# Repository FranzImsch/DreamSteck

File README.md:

### 3x3 Macro Pad

Based on nRF52840

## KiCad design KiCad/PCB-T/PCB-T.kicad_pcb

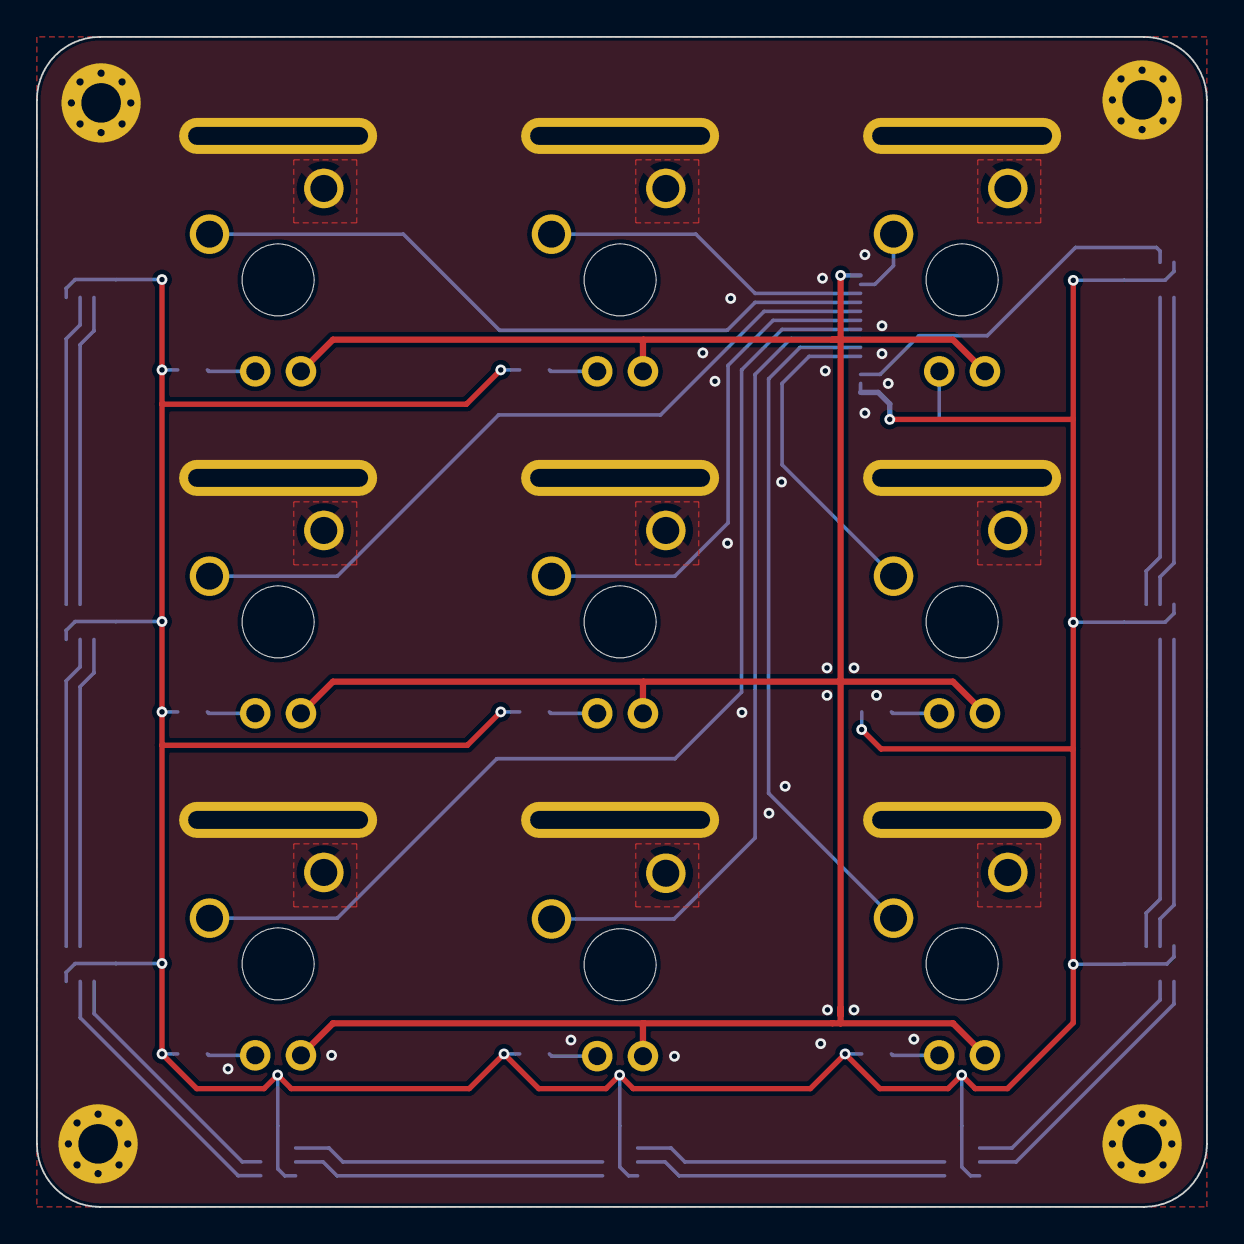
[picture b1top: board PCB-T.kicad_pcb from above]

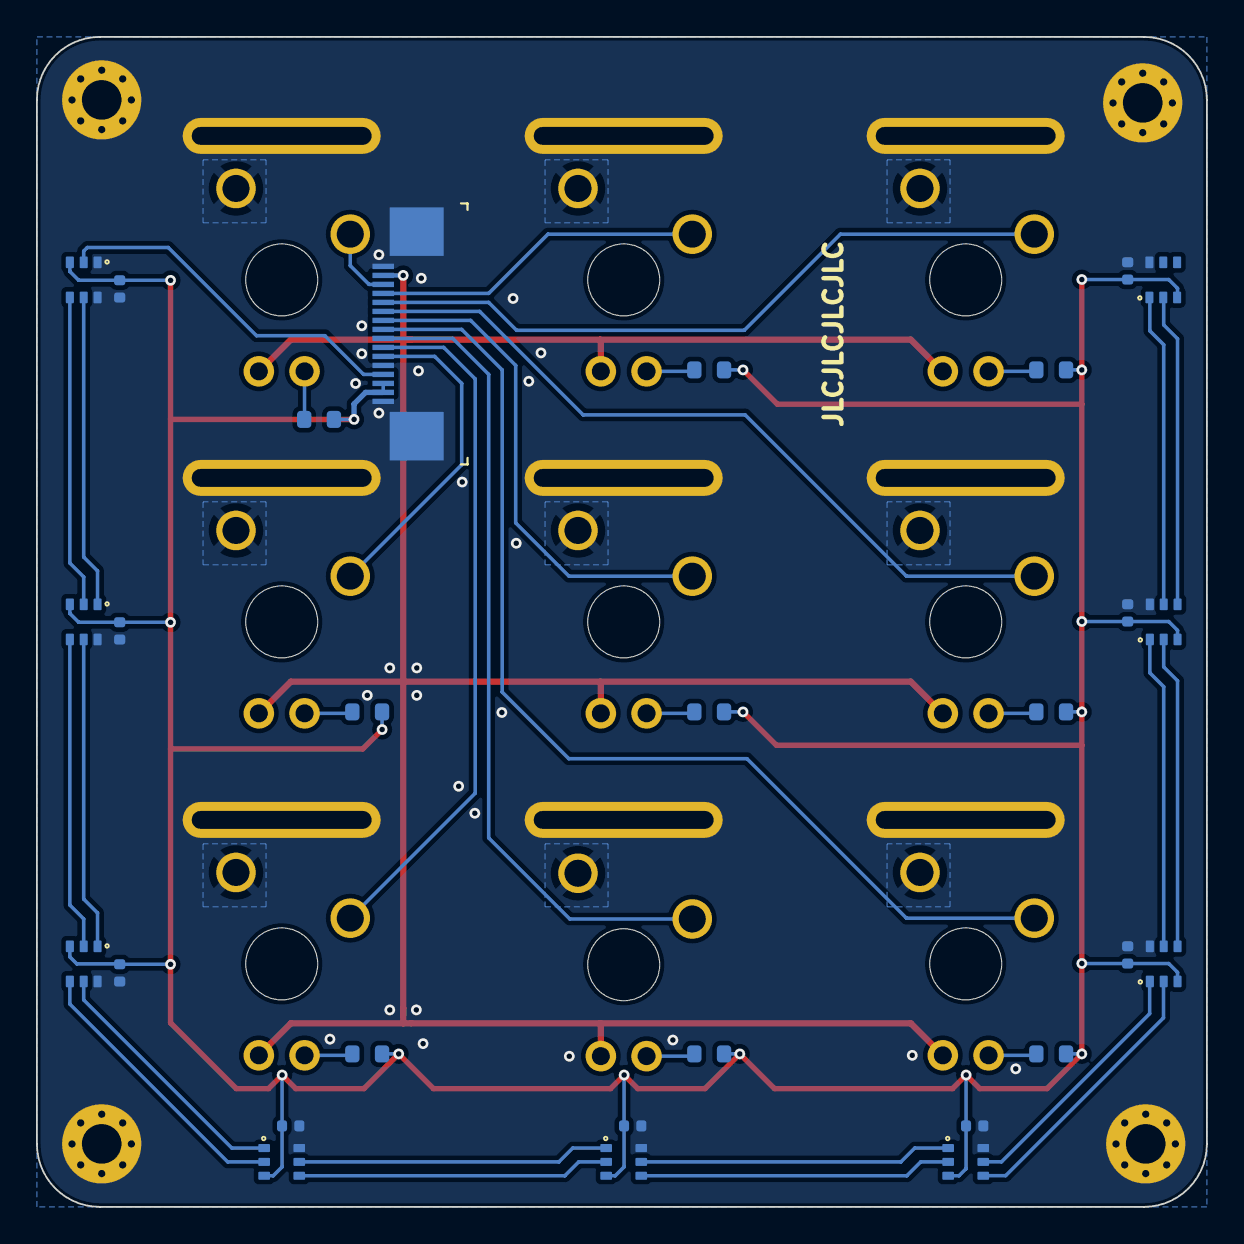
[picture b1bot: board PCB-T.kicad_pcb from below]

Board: 2 copper layers, 65.0 x 65.0 mm, 50 parts (32 on the bottom side), 21 nets.

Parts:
C37, C38, C39, C40, C41, C42, C43, C44, C45: 100n; C_0402_1005Metric_NoSilk
H5, H6, H7, H8: M2; MountingHole_2.2mm_M2_Pad_Via_NoSilk
J5: Conn_01x16_MountingPin; 68711614022
J6, J7, J8, J9, J10, J11, J12, J13, J14: OLED Slot; Plated_Slot_10x1mm
R33, R35, R36, R37, R38, R39, R40, R41, R42: R_Small; R_0603_1608Metric_NoSilk
SW2, SW3, SW4, SW5, SW6, SW7, SW8, SW9, SW10: MX Blue (LED); SW_Cherry_MX_1.00u_Plate_NoSilk
U9, U10, U11, U12, U13, U14, U15, U16, U17: WS2816

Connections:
GND: C37.2, C38.2, C39.2, C40.2, C41.2, C42.2, C43.2, C44.2, C45.2, H5.1, H6.1, H7.1, H8.1, J5.1, J5.5, J5.16, J5.MP (MountPin), J6.1, J7.1, J8.1, J9.1, J10.1, J11.1, J12.1, J13.1, J14.1, SW2.1, SW3.1, SW4.1, SW5.1, SW6.1, SW7.1, SW8.1, SW9.1, SW10.1, U9.1 (BI), U9.6 (GND), U10.6 (GND), U11.6 (GND), U12.6 (GND), U13.6 (GND), U14.6 (GND), U15.6 (GND), U16.6 (GND), U17.6 (GND)
LED-VCC: C37.1, C38.1, C39.1, C40.1, C41.1, C42.1, C43.1, C44.1, C45.1, J5.2, J5.3, R33.1, R35.1, R36.1, R37.1, R38.1, R39.1, R40.1, R41.1, R42.1, U9.3 (VCC), U10.3 (VCC), U11.3 (VCC), U12.3 (VCC), U13.3 (VCC), U14.3 (VCC), U15.3 (VCC), U16.3 (VCC), U17.3 (VCC)
LEDs_N: J5.15, SW2.3 (K), SW3.3 (K), SW4.3 (K), SW5.3 (K), SW6.3 (K), SW7.3 (K), SW8.3 (K), SW9.3 (K), SW10.3 (K)
unnamed: R33.2, SW2.4 (A)
unnamed: R35.2, SW3.4 (A)
unnamed: R36.2, SW4.4 (A)
unnamed: R37.2, SW5.4 (A)
unnamed: R38.2, SW6.4 (A)
unnamed: R39.2, SW7.4 (A)
unnamed: R40.2, SW8.4 (A)
unnamed: R41.2, SW9.4 (A)
SW1: J5.6, SW9.2
SW2: J5.7, SW10.2
SW3: J5.8, SW7.2
SW4: J5.9, SW4.2
SW5: J5.10, SW6.2
SW6: J5.11, SW3.2
SW7: J5.12, SW2.2
SW8: J5.13, SW5.2
SW9: J5.14, SW8.2
WS-DATA: J5.4, U9.2 (DI)

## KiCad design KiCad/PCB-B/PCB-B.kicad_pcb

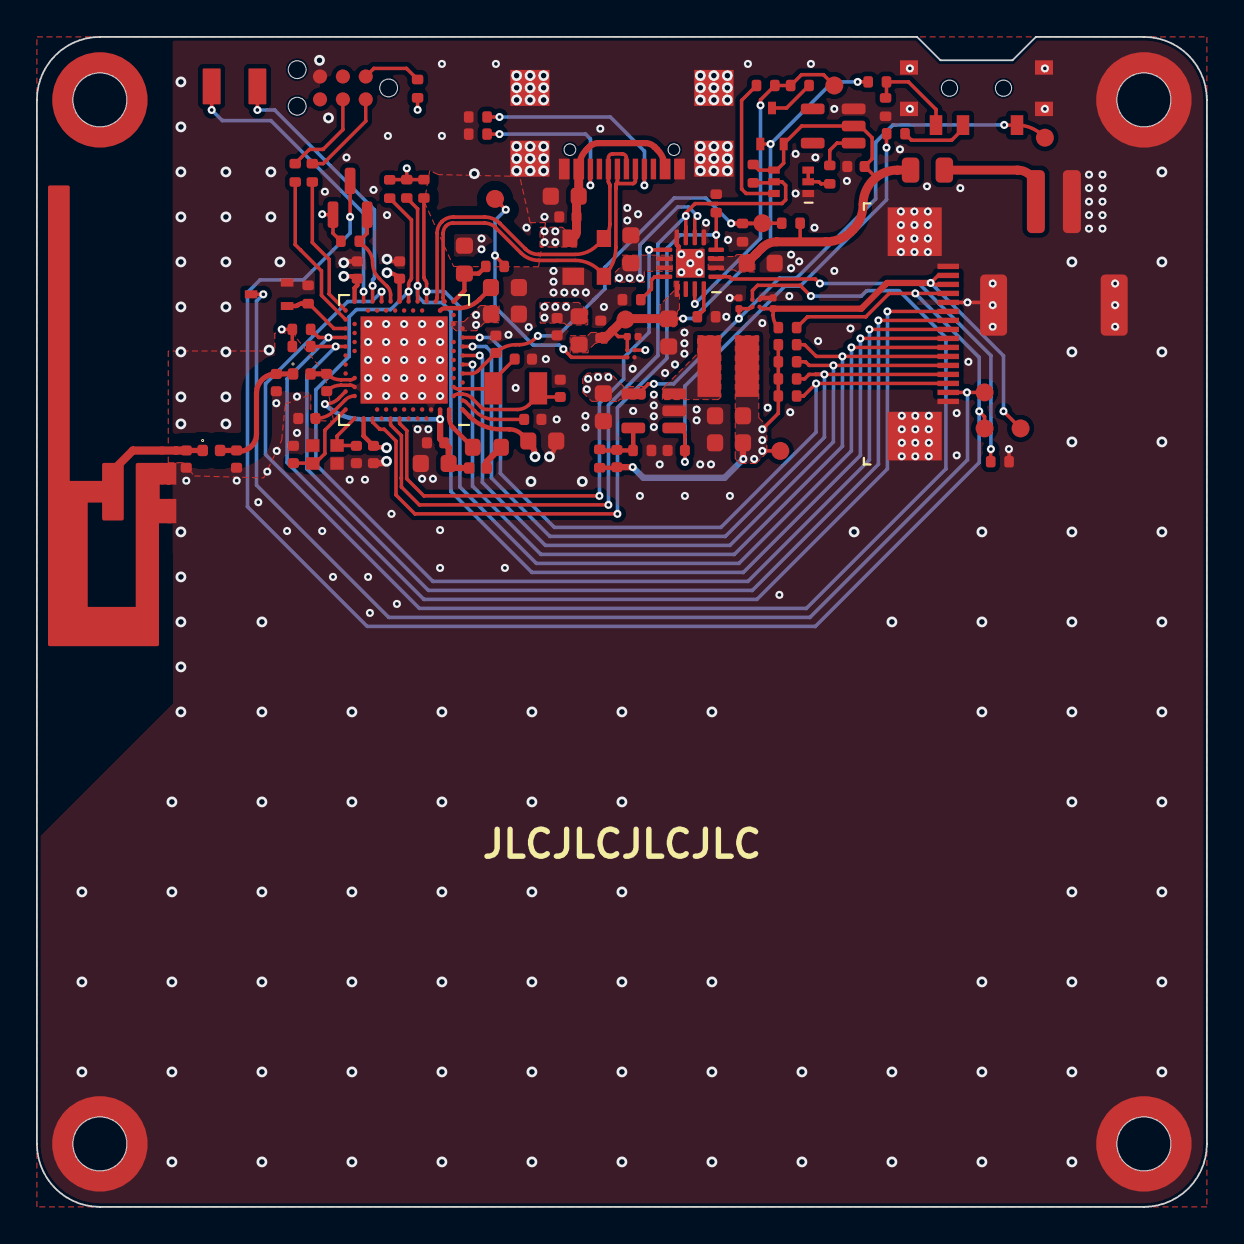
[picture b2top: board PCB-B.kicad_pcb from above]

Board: 4 copper layers, 65.0 x 65.0 mm, 111 parts (0 on the bottom side), 65 nets.

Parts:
AE2: Antenna_Shield; Texas_SWRR034C_2.4GHz_Right
C1: 0.8p; C_0402_1005Metric_NoSilk
C2: 1µF; C_0603_1608Metric_NoSilk
C3: 1µF; C_0402_1005Metric_NoSilk
C4: 10n; C_0402_1005Metric_NoSilk
C5, C7, C21, C28, C29, C30, C36: 100n; C_0402_1005Metric_NoSilk
C6: 0.5p; C_0402_1005Metric_NoSilk
C8: 6µ8; C_0603_1608Metric_NoSilk
C9, C25, C26: 4µ7; C_0603_1608Metric_NoSilk
C10, C11, C32: 10µ; C_0603_1608Metric_NoSilk
C12: 22µ; C_0603_1608Metric_NoSilk
C13: 6p8; C_0402_1005Metric_NoSilk
C14: 4.7µ; C_0603_1608Metric_NoSilk
C15, C16: 15p; C_0402_1005Metric_NoSilk
C17, C18: 4p; C_0402_1005Metric_NoSilk
C19, C20: TBD; C_0402_1005Metric_NoSilk
C22: 47n; C_0402_1005Metric_NoSilk
C23, C27: 1µ; C_0603_1608Metric_NoSilk
C24: 100p; C_0402_1005Metric_NoSilk
C31, C33, C34: 1µ; C_0201_0603Metric_NoSilk
C35: 22n; C_0402_1005Metric_NoSilk
D1: BAT54CW; SOT-323_SC-70_NoSilk
F1: 0.8A; Fuse_0805_2012Metric_NoSilk
FB1: 120R; L_0603_1608Metric_NoSilk
H1, H2, H3, H4: M2; Mounting_Wuerth_WA-SMSI-M2_H8mm_9774080243_NoSilk
J1: USB4110-GF-A; GCT_USB4110-GF-A
J2: Conn_01x02_MountingPin; JST_PH_S2B-PH-SM4-TB_1x02-1MP_P2.00mm_Horizontal
J3: Conn_02x03_TC2030; Tag-Connect_TC2030-IDC-NL_2x03_P1.27mm_Vertical_NoSilk
J4: Conn_01x16_MountingPin; 68711614022
L2: 2µ2; L_Wuerth_MAPI-3012_NoSilk
L4: 10µ; L_0603_1608Metric_NoSilk
L5: 15n; L_0402_1005Metric_NoSilk
L6: 4n7; L_0402_1005Metric_Polarised_NoSilk_Dot
L7: TBD; L_0402_1005Metric_Polarised_NoSilk_Dot
Q1: BSS138; SOT-23_NoSilk
Q2: BSD235C; SOT-363_SC-70-6_NoSilk
Q3: PJC7400; SOT-323_SC-70_NoSilk
R1, R4: 5k1; R_0402_1005Metric_NoSilk
R2, R3: 1kΩ; R_0402_1005Metric_NoSilk
R5, R31: 4R7; R_0402_1005Metric_NoSilk
R6: 200k; R_0402_1005Metric_NoSilk
R7, R32, R34: 100k; R_0402_1005Metric_NoSilk
R8: 470k; R_0402_1005Metric_NoSilk
R9, R11, R12, R14, R17: 1M; R_0402_1005Metric_NoSilk
R13, R20, R21, R22, R23, R24, R25, R26, R27, R28: 10k; R_0402_1005Metric_NoSilk
R15: 1k2; R_0402_1005Metric_NoSilk
R16: 1k7; R_0402_1005Metric_NoSilk
R18: 10M; R_0402_1005Metric_NoSilk
R19: 2M2; R_0402_1005Metric_NoSilk
R29, R30: 22Ω; R_0402_1005Metric_NoSilk
SW1: SW_SPDT; 450404015514
TH1: 10k; R_0402_1005Metric_NoSilk
TP1: GPIO_TP_1; TestPoint_Pad_1.0x2.0mm_NoSilk
TP2: GPIO_TP_2; TestPoint_Pad_1.0x2.0mm_NoSilk
TP3, TP4, TP5, TP6, TP7, TP8, TP9, TP10, TP11: TestPoint; TestPoint_Pad_D1.0mm_NoSIlk
U1: nRF52840; Nordic_AQFN-73-1EP_7x7mm_P0.5mm_NoSilk
U2: BQ24075RGT; VQFN-16-1EP_3x3mm_P0.5mm_EP1.6x1.6mm_NoSilk
U3, U5: TCK106AG; WCSPD-4_NoSilk
U4: SR05.TCT; SOT143-4L-slim
U6: TLV62568DBV; SOT-23-5_NoSilk
U7: S-1009C32I-M5T1U; SOT-23-5_NoSilk
U8: LiIon-5x34x50
Y1: 32.768k; Crystal_SMD_3215-2Pin_NoSilk
Y2: 32M; OSC_XRCGB24M000F3M01R0

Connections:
+1V8: C10.1, C11.1, C13.1, C26.1, C27.1, C28.1, C29.1, C30.1, L2.2, Q1.1 (G), R3.1, R6.1, R20.1, R21.1, R22.1, R23.1, R24.1, R25.1, R26.1, R27.1, R28.1, R31.1, TP7.1, U1.A22 (VDD), U1.AD14 (VDD), U1.AD23 (VDD), U1.B1 (VDD), U1.W1 (VDD), U1.Y2 (VDDH), U5.B2 (CTRL)
+5V: C9.2, C12.2, C34.1, SW1.1 (A), TP6.1, U2.6 (EN1), U2.10 (OUT), U2.11 (OUT), U3.A2 (VIN), U6.4 (VIN)
/Board Connector/LEDs_N: J4.15, Q3.3 (D), TP9.1
/Board Connector/V_LED: C33.1, J4.2, J4.3, R2.1, TP10.1, U3.A1 (VOUT)
/Board Connector/WS-DATA: J4.4, Q1.3 (D), R2.2, TP11.1
/MCU/1V8': J3.1, R31.2
/MCU/ANT: AE2.1 (A), C20.1, L7.2
/MCU/ANT_FEED: C6.1, C19.1, L6.2, L7.1
/MCU/ANT_nRF: C1.1, L6.1, U1.H23 (ANT)
/MCU/DCC: L4.2, U1.B3 (DCC)
/MCU/DCC_L: L4.1, L5.2
/MCU/DEC1: C21.1, U1.C1 (DEC1)
/MCU/DEC3: C24.1, U1.D23 (DEC3)
/MCU/DEC6: C22.1, C23.1, L5.1, U1.B5 (DEC4), U1.E24 (DEC6)
/MCU/DECUSB: C25.1, U1.AC5 (DECUSB)
/MCU/GPIO_TP_1: TP1.1, U1.AD20 (P0.24)
/MCU/GPIO_TP_2: TP2.1, U1.AD22 (TRACEDATA0/P1.00)
/MCU/SWCLK': J3.4, R30.2
/MCU/SWDIO': J3.2, R29.2
/MCU/VBUS_nRF: C14.1, R5.2, U1.AD2 (VBUS)
/MCU/VBUS_nRF': R5.1, TP8.1, U5.A1 (VOUT)
/MCU/XC1: C17.1, U1.B24 (XC1), Y2.3
/MCU/XC2: C18.1, U1.A23 (XC2), Y2.1
/MCU/XL1: C15.2, U1.D2 (XL1/P0.00), Y1.2
/MCU/XL2: C16.2, U1.F2 (XL2/P0.01), Y1.1
/Power/BAT: F1.2, J2.1
/Power/FB: C13.2, R6.2, R7.1, U6.5 (FB)
/Power/I_{LIM}: R16.1, U2.12 (ILIM)
/Power/I_{SET}: R15.1, U2.16 (ISET)
/Power/NTC: TH1.1, U2.1 (TS)
/Power/SPRVSR: R12.1, U7.1 (Reset/out)
/Power/SW: L2.1, U6.3 (SW)
/Power/SYSOFF: R13.1, R14.2, TP4.1, U2.15 (SYSOFF)
/Power/TLV_(off): R8.2, R9.1, SW1.3 (C)
/Power/TLV_EN: C36.1, R34.2, U6.1 (EN)
/Power/V_PULLUP: D1.3, R14.1
/Power/~SYSON_CTRL: Q2.2 (GN), Q2.3 (DP), R12.2
/Power/~SYSON: Q2.6 (DN), R13.2
/USB/CC1: J1.A5 (CC1), R1.1
/USB/CC2: J1.B5 (CC2), R4.1
/USB/VBUS': C4.1, C7.1, C8.1, FB1.1, J1.A4 (VBUS), J1.A9 (VBUS), J1.B4 (VBUS), J1.B9 (VBUS), U4.4 (VBUS)
BACKLIGHT_LEDs: Q3.1 (G), R32.1, U1.W24 (P1.02)
D_N: J1.A7 (D-), J1.B7 (D-), U1.AD4 (D-), U4.2 (CH1)
D_P: J1.A6 (D+), J1.B6 (D+), U1.AD6 (D+), U4.3 (CH2)
GND: AE2.2 (Shield), C1.2, C2.2, C3.2, C4.2, C5.2, C6.2, C7.2, C8.2, C9.1, C10.2, C11.2, C12.1, C14.2, C15.1, C16.1, C17.2, C18.2, C19.2, C20.2, C21.2, C22.2, C23.2, C24.2, C25.2, C26.2, C27.2, C28.2, C29.2, C30.2, C31.2, C32.1, C33.2, C34.2, C35.2, C36.2, H1.1, H3.1, H4.1, J1.A1 (GND), J1.A12 (GND), J1.B1 (GND), J1.B12 (GND), J1.S1 (SHIELD), J2.2, J2.MP (MountPin), J3.5, J4.1, J4.5, J4.16, J4.MP (MountPin), Q2.1 (SN), Q3.2 (S), R1.2, R4.2, R7.2, R9.2, R15.2, R16.2, R17.2, R19.2, R32.2, SW1.SH (MP), TH1.2, U1.B7 (VSS), U1.EP (VSS), U1.F23 (VSS_PA), U2.5 (EN2), U2.8 (VSS), U2.17 (VSS), U3.B1 (GND), U4.1 (GND), U5.B1 (GND), U6.2 (GND), U7.3 (GND), Y2.2, Y2.4
unnamed: R34.1, SW1.2 (B)
SW1: J4.6, R28.2, U1.U24 (P1.04)
SW2: J4.7, R27.2, U1.R24 (P1.06)
SW3: J4.8, R26.2, U1.AD12 (P0.17)
SW4: J4.9, R25.2, U1.AD10 (P0.15)
SW5: J4.10, R24.2, U1.AD8 (P0.13)
SW6: J4.11, R23.2, U1.L1 (P0.06)
SW7: J4.12, R22.2, U1.N1 (P0.08)
SW8: J4.13, R21.2, U1.R1 (TRACEDATA3/P1.09)
SW9: J4.14, R20.2, U1.U1 (TRACEDATA1/P0.12)
SWCLK: R30.1, U1.AA24 (SWDCLK)
SWDIO: R29.1, U1.AC24 (SWDIO)
VBAT: C3.1, C32.2, D1.2, F1.1, Q2.4 (SP), R11.1, R18.1, U2.2 (BAT), U2.3 (BAT), U7.2 (Input)
VBAT_ADC: C35.1, R18.2, R19.1, TP5.1, U1.J1 (AIN2/P0.04)
VBUS: C2.1, C5.1, C31.1, D1.1, FB1.2, R8.1, TP3.1, U2.13 (IN), U5.A2 (VIN)
WS-DIN: Q1.2 (S), R3.2, U1.AD16 (P0.20)
WS-EN: U1.AD18 (P0.22), U3.B2 (CTRL)
~CE: R17.1, U1.A20 (P1.10), U2.4 (~CE)
~CHG: U1.A14 (P1.15), U2.9 (~CHG)
~PGOOD: Q2.5 (GP), R11.2, U1.A16 (P1.13), U2.7 (~PGOOD)

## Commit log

2023-03-04 initialised repo
